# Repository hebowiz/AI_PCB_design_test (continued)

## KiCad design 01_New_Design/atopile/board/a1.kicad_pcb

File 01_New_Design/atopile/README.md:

# A-1 atopile設計

TXD/RXD/RTS/CTSのUSB-UART基板です。ユーザー指示により板厚を1.6 mmへ変更しました。22×50 mm、2層、全部品を表面に配置しています。

最終ERC/DRCは違反0件、未配線0件です。ただし、USB差動配線、水晶周辺、ビアとパッドの重なり、機械寸法・実装条件の確認が残っています。製造承認済みではありません。詳細は[設計結果](reports/design_review.md)を参照してください。

| 成果物 | パス |
| --- | --- |
| 最終PCB | `board/a1.kicad_pcb` |
| プロジェクト・回路図 | `board/a1.kicad_pro`、`board/a1.kicad_sch` |
| atopile回路 | `board/main.ato`、`board/parts/parts.ato` |
| 接続・配置の原記述 | `scripts/design.py`、`board/design.json` |
| 回路図PDF | `reports/schematic.pdf` |
| 裸基板の画像 | `reports/board-top.png` |
| 表裏の配線図 | `reports/board-front.svg`、`reports/board-back.svg` |
| 検査結果 | `reports/erc.json`、`reports/drc.json`、`reports/connectivity.json` |
| 部品表・ピン接続 | `reports/bom.csv`、`reports/pin_net.csv` |
| 製造レビュー用 | `manufacturing/review-only/`、`manufacturing/A1-REVIEW-ONLY.zip` |
| 経緯 | `reports/work_log.md`、`reports/decision_log.md`、`reports/discussion_log.md` |

## 実行環境と再検査

atopileは`docs/atopile_recovery.md`で修復された0.15.8を使います。`scripts/ato.ps1`は共有Git管理ディレクトリから元リポジトリの`.setup-local/atopile-rebuild`を見つけ、設定・ログをA-1の`.local/`へ分離します。別の配置では`A1_ATOPILE_REBUILD`で指定できます。通常のPATHにある`ato`は使用していません。

KiCadは10.0.8、同梱Pythonは3.11.5、Freeroutingは2.1.0、Javaは21.0.13.9です。次のコマンドはリポジトリのルートから実行します。

```powershell
$cli = "$env:LOCALAPPDATA/Programs/KiCad/10.0/bin/kicad-cli.exe"
$py = "$env:LOCALAPPDATA/Programs/KiCad/10.0/bin/python.exe"
$env:PYTHONUTF8 = '1'
& $cli sch erc --format json --exit-code-violations -o 01_New_Design/atopile/reports/erc.json 01_New_Design/atopile/board/a1.kicad_sch
& $cli sch export netlist --format kicadxml -o 01_New_Design/atopile/reports/schematic.net.xml 01_New_Design/atopile/board/a1.kicad_sch
& $py 01_New_Design/atopile/scripts/check_connectivity.py
& $cli pcb drc --severity-all --format json --exit-code-violations -o 01_New_Design/atopile/reports/drc.json 01_New_Design/atopile/board/a1.kicad_pcb
& $py 01_New_Design/atopile/scripts/layout.py verify
& ./01_New_Design/atopile/scripts/manufacturing.ps1
```

製造出力スクリプトはファイルをローカルで生成するだけで、発注やアップロードはしません。出力の内容と使用条件は`manufacturing/README.md`を参照してください。

## 回路生成と配置・配線の再現範囲

`scripts/design.py`は原記述からatomic部品、BOM、接続マニフェストを生成します。続く`./01_New_Design/atopile/scripts/ato.ps1 build --verbose`は`board/layouts/default/default.kicad_pcb`を生成します。最終PCBとは別ファイルです。

`scripts/layout.py prep`は配置とUSB固定配線を作り、`board/a1.kicad_pcb`を上書きします。完成済みPCBや人が変更したPCBにそのまま実行しないでください。今回の最終配線はFreeroutingのSESを取り込んだ後、未接続とGND、サーマル接続を補修した結果です。生成から最終状態までを一度に再現する単一コマンドは用意していません。

初回DSN/SESは`board/a1.dsn`と`board/a1.ses`です。Freerouting単独の未配線0は、KiCad取り込み後の未配線0を意味しません。最終成果物は補修後の`board/a1.kicad_pcb`です。`repair.dsn`と`repair2.dsn`は完走しなかった追加配線の入力証跡です。

FreeroutingはA-1内の一時ディレクトリを作業ディレクトリにし、次の条件で実行しました。

```text
java -Xmx6g -Djava.awt.headless=true -jar freerouting-2.1.0.jar -de input.dsn -do output.ses -mp 30 -mt 2 -da -l en --gui.enabled=false --user_data_path=<A-1内の作業ディレクトリ>
```

`freerouting.json`ではGUIとoptimizerを無効にし、profileのemail/idを空にしました。パス数の指定に反して継続する挙動があったため、停滞した試行は中断しています。ログは`reports/router-attempt*.log`に保存しました。

最終フットプリントは`board/A1.pretty`に保存しています。元のatomic部品のフットプリントに対して、シルクを整理し、5パッドのGNDゾーン接続を直接接続へ変更しました。銅箔パッドの位置・番号・寸法は変更していません。ローカルライブラリとの照合も含めてDRCを実行しています。

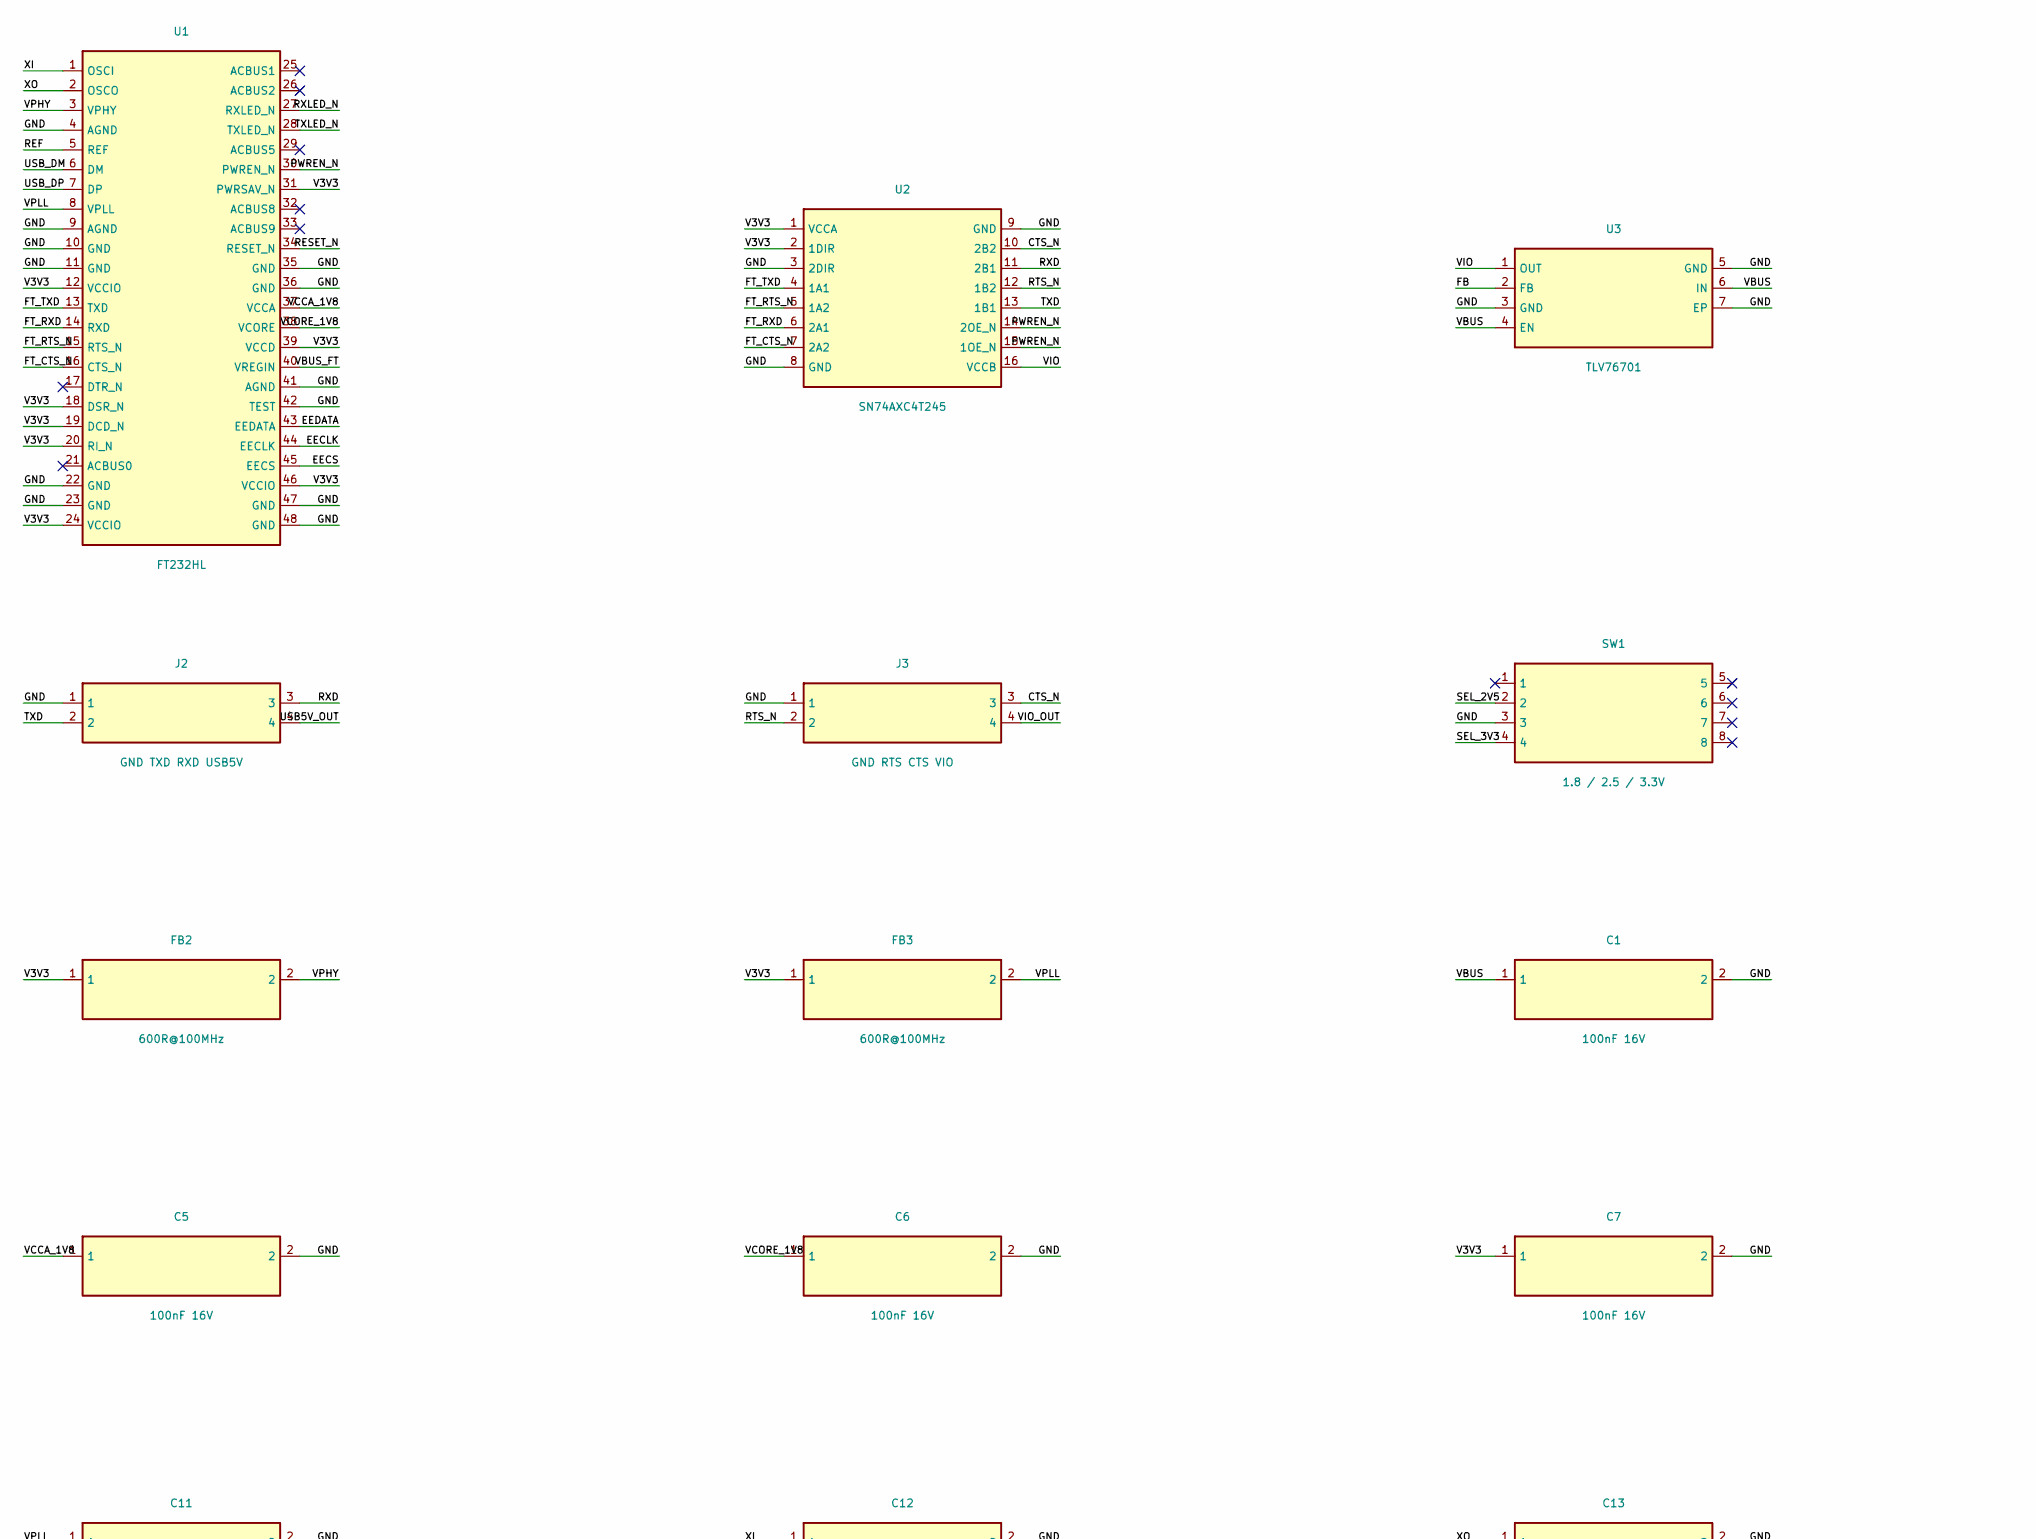
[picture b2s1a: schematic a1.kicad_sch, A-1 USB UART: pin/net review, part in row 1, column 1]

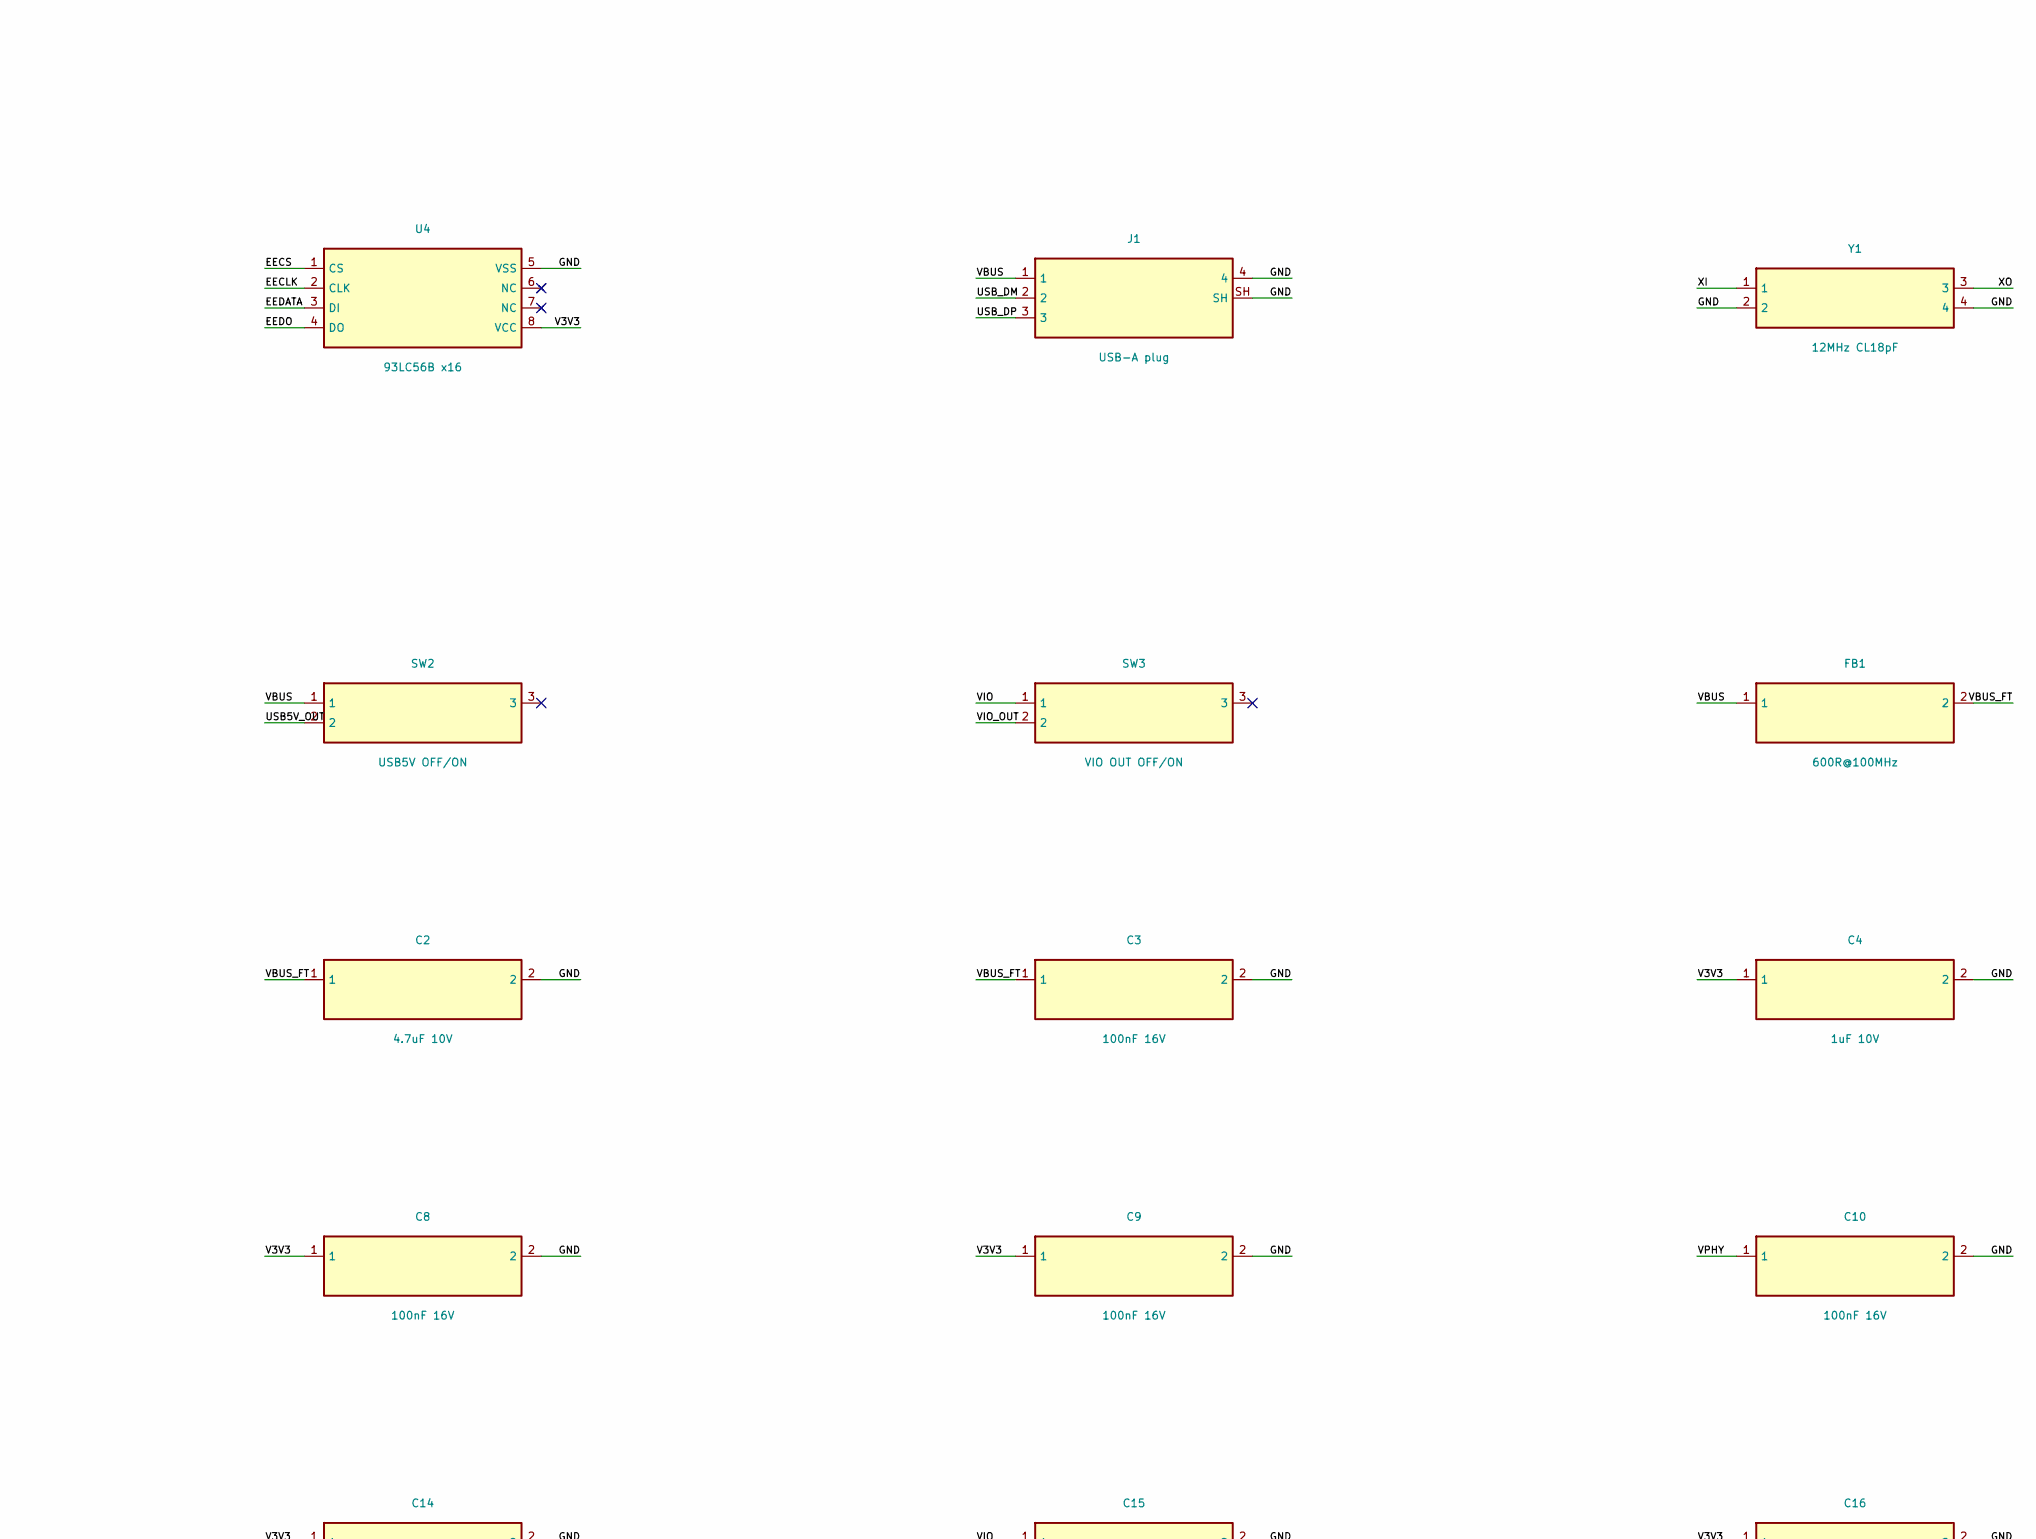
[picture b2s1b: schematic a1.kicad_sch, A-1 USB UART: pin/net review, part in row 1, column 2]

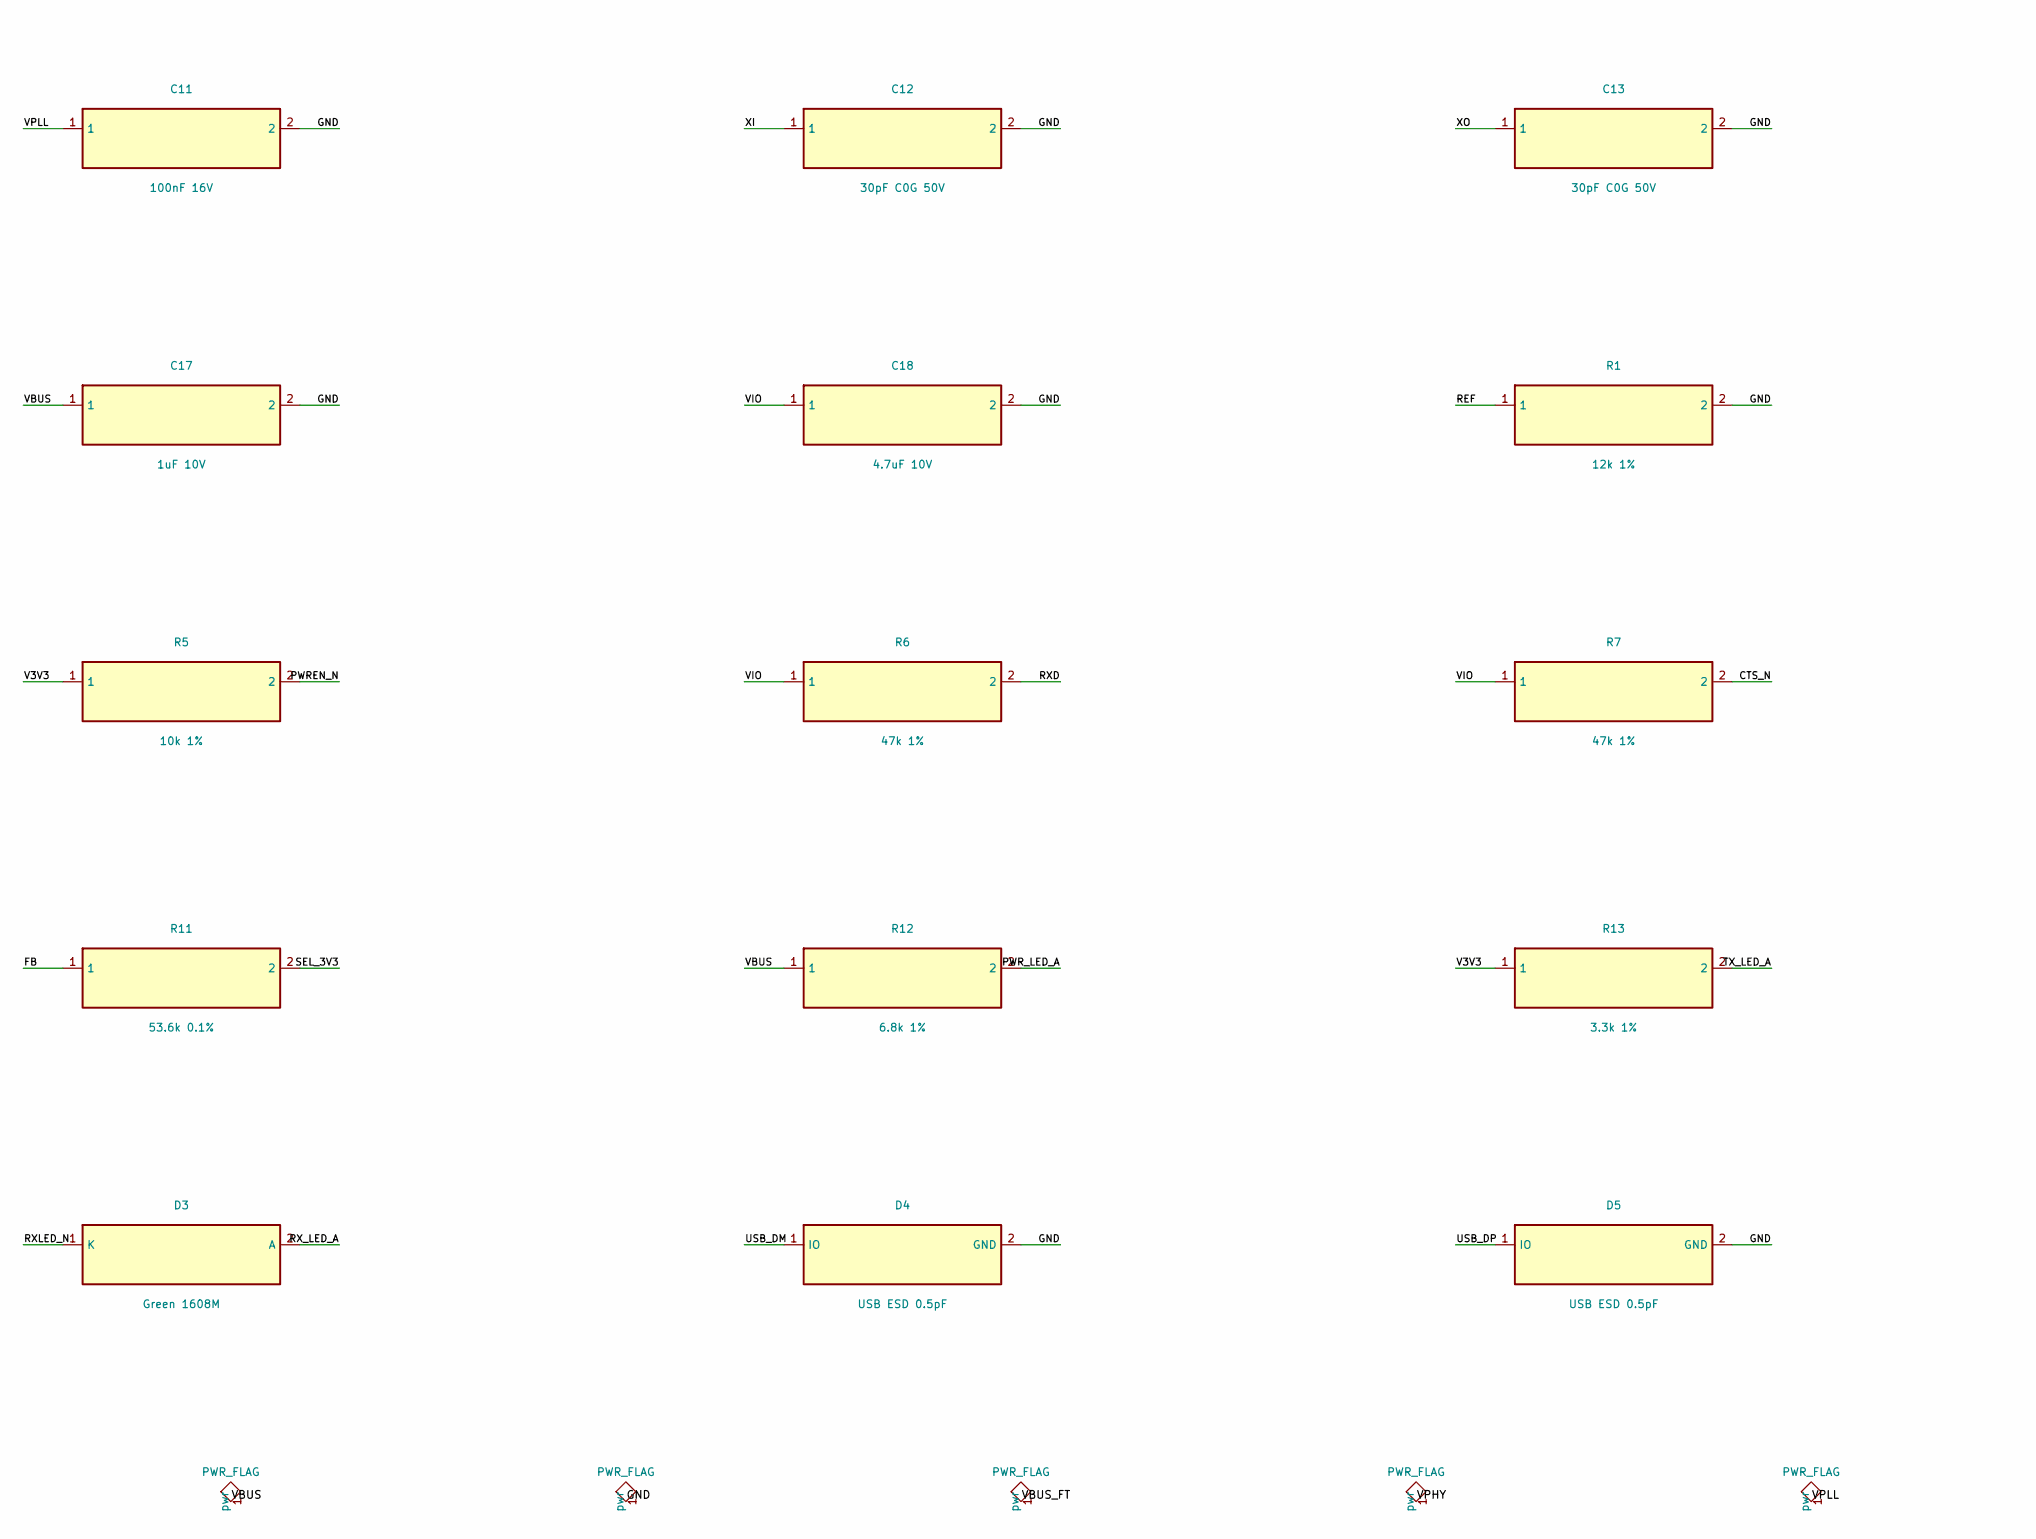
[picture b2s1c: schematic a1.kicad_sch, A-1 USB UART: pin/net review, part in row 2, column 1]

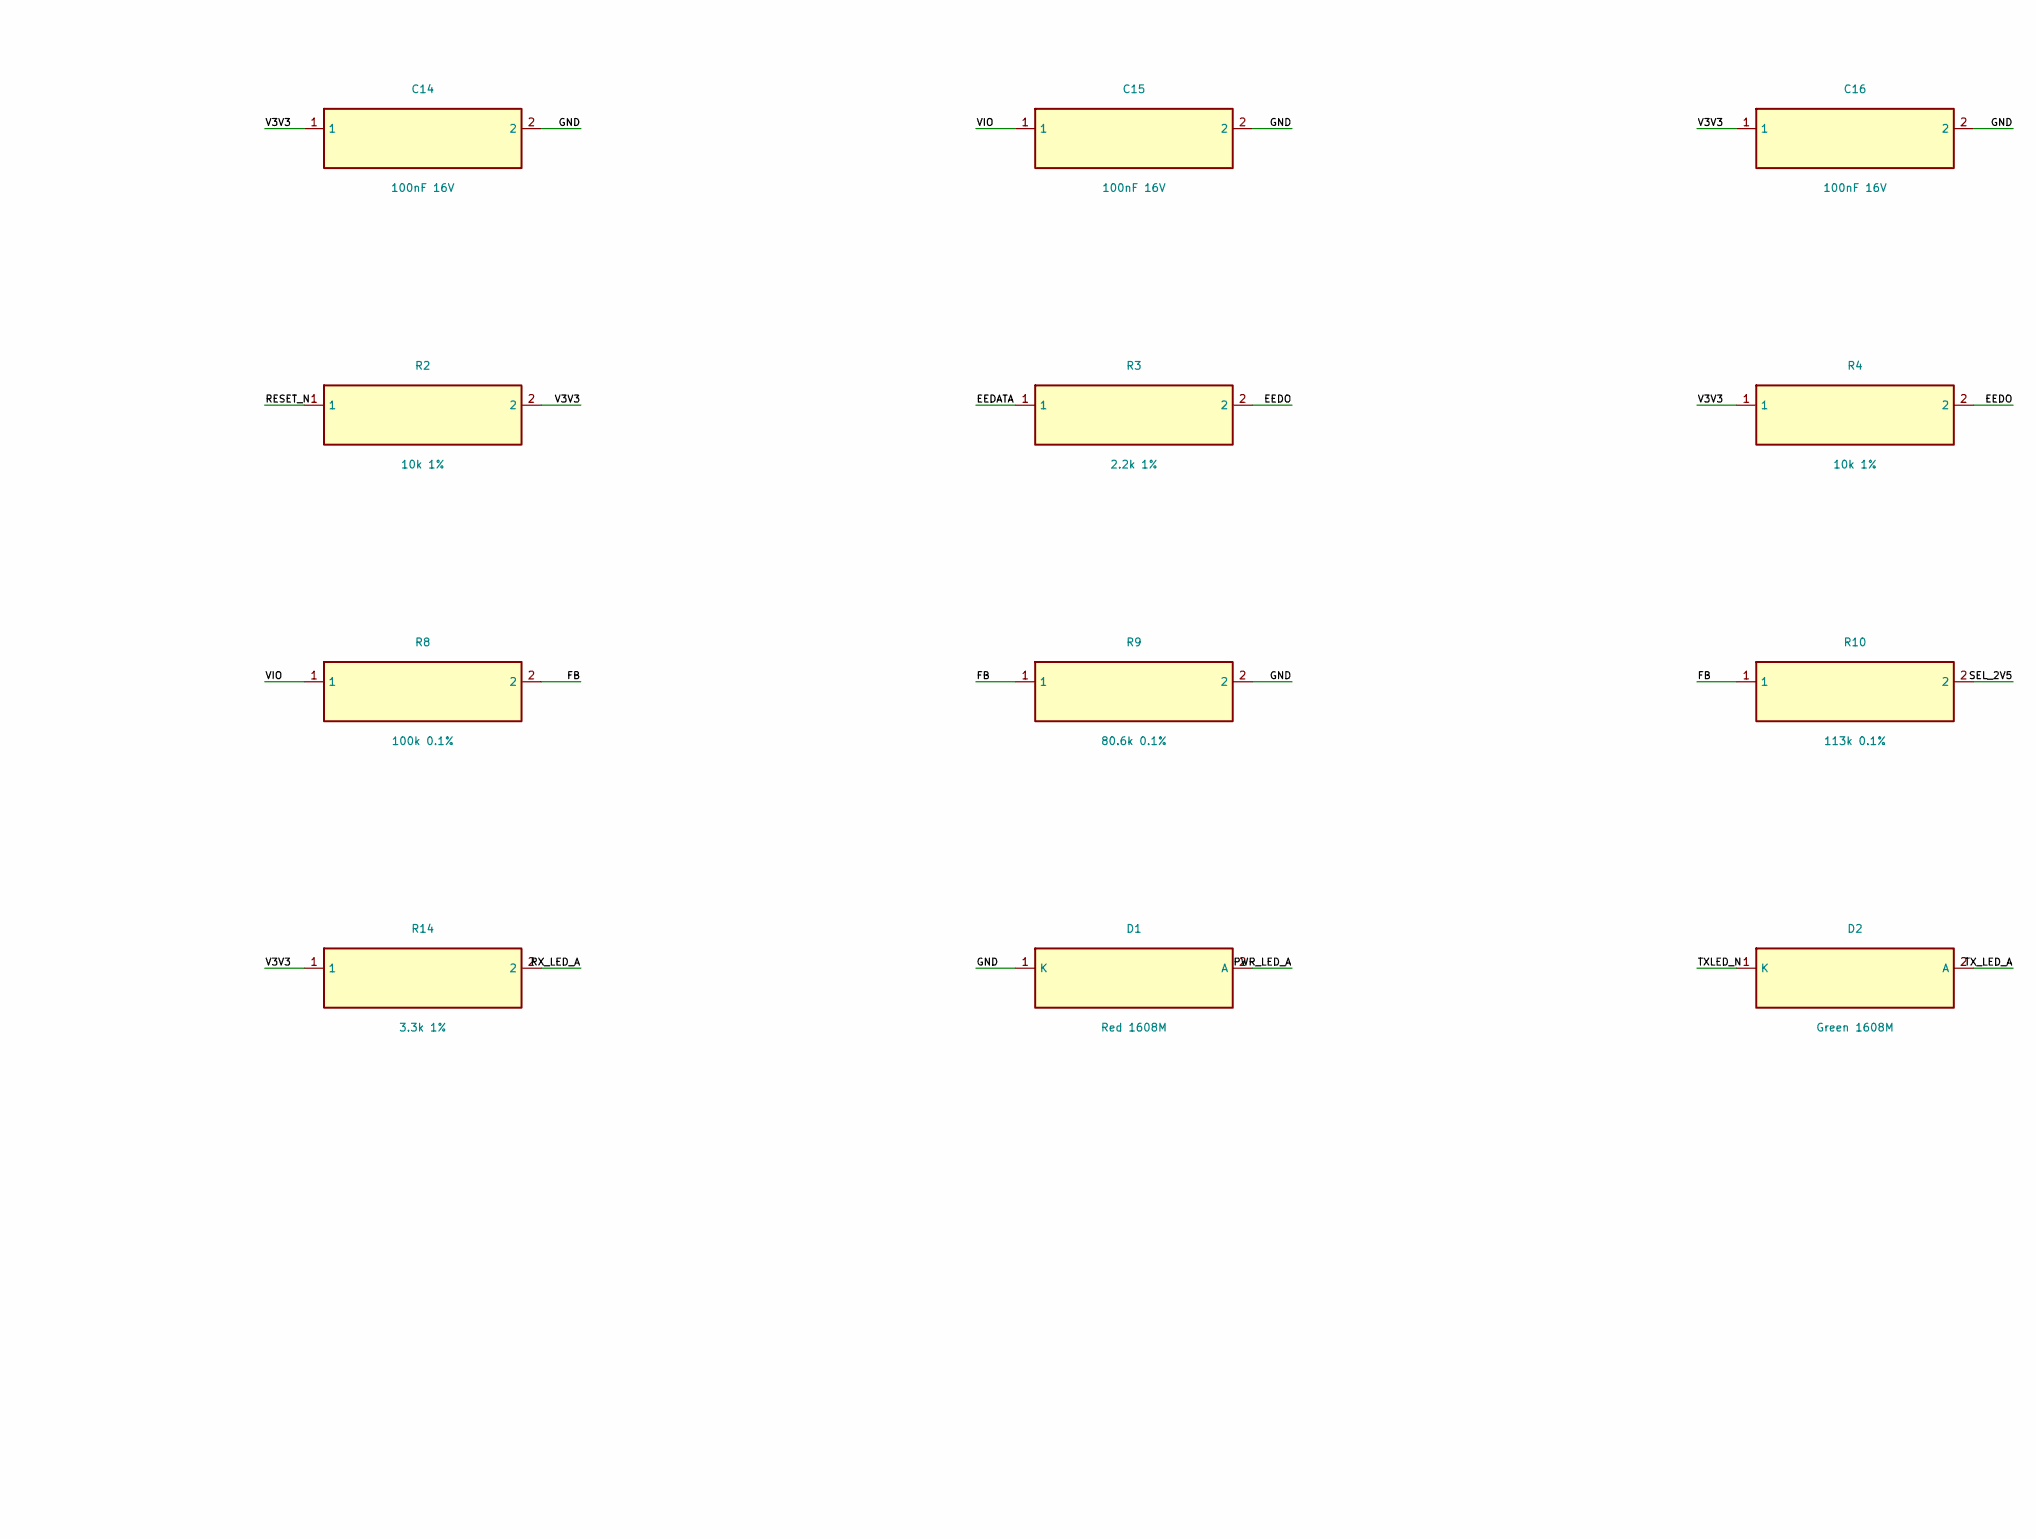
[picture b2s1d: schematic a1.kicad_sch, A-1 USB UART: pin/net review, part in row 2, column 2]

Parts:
C1: 100nF 16V; C1; MPN GRM155R71C104KA88D
C2: 4.7uF 10V; C2; MPN GRM188R61A475KE15D
C3: 100nF 16V; C3; MPN GRM155R71C104KA88D
C4: 1uF 10V; C4; MPN GRM188R61A105KA61D
C5: 100nF 16V; C5; MPN GRM155R71C104KA88D
C6: 100nF 16V; C6; MPN GRM155R71C104KA88D
C7: 100nF 16V; C7; MPN GRM155R71C104KA88D
C8: 100nF 16V; C8; MPN GRM155R71C104KA88D
C9: 100nF 16V; C9; MPN GRM155R71C104KA88D
C10: 100nF 16V; C10; MPN GRM155R71C104KA88D
C11: 100nF 16V; C11; MPN GRM155R71C104KA88D
C12: 30pF C0G 50V; C12; MPN GRM1555C1H300JA01D
C13: 30pF C0G 50V; C13; MPN GRM1555C1H300JA01D
C14: 100nF 16V; C14; MPN GRM155R71C104KA88D
C15: 100nF 16V; C15; MPN GRM155R71C104KA88D
C16: 100nF 16V; C16; MPN GRM155R71C104KA88D
C17: 1uF 10V; C17; MPN GRM188R61A105KA61D
C18: 4.7uF 10V; C18; MPN GRM188R61A475KE15D
D1: Red 1608M; D1; MPN LTST-C190KRKT
D2: Green 1608M; D2; MPN LTST-C190KGKT
D3: Green 1608M; D3; MPN LTST-C190KGKT
D4: USB ESD 0.5pF; D4; MPN TPD1E05U06DYAR
D5: USB ESD 0.5pF; D5; MPN TPD1E05U06DYAR
FB1: 600R@100MHz; FB1; MPN BLM15AG601SN1D
FB2: 600R@100MHz; FB2; MPN BLM15AG601SN1D
FB3: 600R@100MHz; FB3; MPN BLM15AG601SN1D
J1: USB-A plug; J1; MPN 0480372200
J2: GND TXD RXD USB5V; J2; MPN TSM-104-01-L-SH
J3: GND RTS CTS VIO; J3; MPN TSM-104-01-L-SV
R1: 12k 1%; R1; MPN RC0402FR-0712KL
R2: 10k 1%; R2; MPN RC0402FR-0710KL
R3: 2.2k 1%; R3; MPN RC0402FR-072K2L
R4: 10k 1%; R4; MPN RC0402FR-0710KL
R5: 10k 1%; R5; MPN RC0402FR-0710KL
R6: 47k 1%; R6; MPN RC0402FR-0747KL
R7: 47k 1%; R7; MPN RC0402FR-0747KL
R8: 100k 0.1%; R8; MPN RT0402BRD07100KL
R9: 80.6k 0.1%; R9; MPN RT0402BRD0780K6L
R10: 113k 0.1%; R10; MPN RT0402BRD07113KL
R11: 53.6k 0.1%; R11; MPN RT0402BRD0753K6L
R12: 6.8k 1%; R12; MPN RC0402FR-076K8L
R13: 3.3k 1%; R13; MPN RC0402FR-073K3L
R14: 3.3k 1%; R14; MPN RC0402FR-073K3L
SW1: 1.8 / 2.5 / 3.3V; SW1; MPN JS203011SCQN
SW2: USB5V OFF/ON; SW2; MPN PCM12SMTR
SW3: VIO OUT OFF/ON; SW3; MPN PCM12SMTR
U1: FT232HL; U1; MPN FT232HL-REEL
U2: SN74AXC4T245; U2; MPN SN74AXC4T245PWR
U3: TLV76701; U3; MPN TLV76701DRVR
U4: 93LC56B x16; U4; MPN 93LC56BT-I/SN
Y1: 12MHz CL18pF; Y1; MPN ABM8-12.000MHZ-B1U-T

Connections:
1: SW1.1
3: SW2.3
5: SW1.5
6: U4.6 (NC)
7: U4.7 (NC)
8: SW1.8
17: U1.17 (DTR_N)
21: U1.21 (ACBUS0)
25: U1.25 (ACBUS1)
26: U1.26 (ACBUS2)
29: U1.29 (ACBUS5)
32: U1.32 (ACBUS8)
33: U1.33 (ACBUS9)
CTS_N: J3.3, R7.2, U2.10 (2B2)
EECLK: U1.44 (EECLK), U4.2 (CLK)
EECS: U1.45 (EECS), U4.1 (CS)
EEDATA: R3.1, U1.43 (EEDATA), U4.3 (DI)
EEDO: R3.2, R4.2, U4.4 (DO)
FB: R8.2, R9.1, R10.1, R11.1, U3.2 (FB)
FT_CTS_N: U1.16 (CTS_N), U2.7 (2A2)
FT_RTS_N: U1.15 (RTS_N), U2.5 (1A2)
FT_RXD: U1.14 (RXD), U2.6 (2A1)
FT_TXD: U1.13 (TXD), U2.4 (1A1)
GND: C1.2, C2.2, C3.2, C4.2, C5.2, C6.2, C7.2, C8.2, C9.2, C10.2, C11.2, C12.2, C13.2, C14.2, C15.2, C16.2, C17.2, C18.2, D1.1 (K), D4.2 (GND), D5.2 (GND), J1.4, J1.SH, J2.1, J3.1, R1.2, R9.2, SW1.3, U1.4 (AGND), U1.9 (AGND), U1.10 (GND), U1.11 (GND), U1.22 (GND), U1.23 (GND), U1.35 (GND), U1.36 (GND), U1.41 (AGND), U1.42 (TEST), U1.47 (GND), U1.48 (GND), U2.3 (2DIR), U2.8 (GND), U2.9 (GND), U3.3 (GND), U3.5 (GND), U3.7 (EP), U4.5 (VSS), Y1.2, Y1.4
PWREN_N: R5.2, U1.30 (PWREN_N), U2.14 (2OE_N), U2.15 (1OE_N)
PWR_LED_A: D1.2 (A), R12.2
REF: R1.1, U1.5 (REF)
RESET_N: R2.1, U1.34 (RESET_N)
RTS_N: J3.2, U2.12 (1B2)
RXD: J2.3, R6.2, U2.11 (2B1)
RXLED_N: D3.1 (K), U1.27 (RXLED_N)
RX_LED_A: D3.2 (A), R14.2
SEL_2V5: R10.2, SW1.2
SEL_3V3: R11.2, SW1.4
TXD: J2.2, U2.13 (1B1)
TXLED_N: D2.1 (K), U1.28 (TXLED_N)
TX_LED_A: D2.2 (A), R13.2
USB5V_OUT: J2.4, SW2.2
USB_DM: D4.1 (IO), J1.2, U1.6 (DM)
USB_DP: D5.1 (IO), J1.3, U1.7 (DP)
V3V3: C4.1, C7.1, C8.1, C9.1, C14.1, C16.1, FB2.1, FB3.1, R2.2, R4.1, R5.1, R13.1, R14.1, U1.12 (VCCIO), U1.18 (DSR_N), U1.19 (DCD_N), U1.20 (RI_N), U1.24 (VCCIO), U1.31 (PWRSAV_N), U1.39 (VCCD), U1.46 (VCCIO), U2.1 (VCCA), U2.2 (1DIR), U4.8 (VCC)
VBUS: C1.1, C17.1, FB1.1, J1.1, R12.1, SW2.1, U3.4 (EN), U3.6 (IN)
VBUS_FT: C2.1, C3.1, FB1.2, U1.40 (VREGIN)
VCCA_1V8: C5.1, U1.37 (VCCA)
VCORE_1V8: C6.1, U1.38 (VCORE)
VIO: C15.1, C18.1, R6.1, R7.1, R8.1, SW3.1, U2.16 (VCCB), U3.1 (OUT)
VIO_OUT: J3.4, SW3.2
VPHY: C10.1, FB2.2, U1.3 (VPHY)
VPLL: C11.1, FB3.2, U1.8 (VPLL)
XI: C12.1, U1.1 (OSCI), Y1.1
XO: C13.1, U1.2 (OSCO), Y1.3
vio_switch-3: SW3.3
voltage_select-6: SW1.6
voltage_select-7: SW1.7

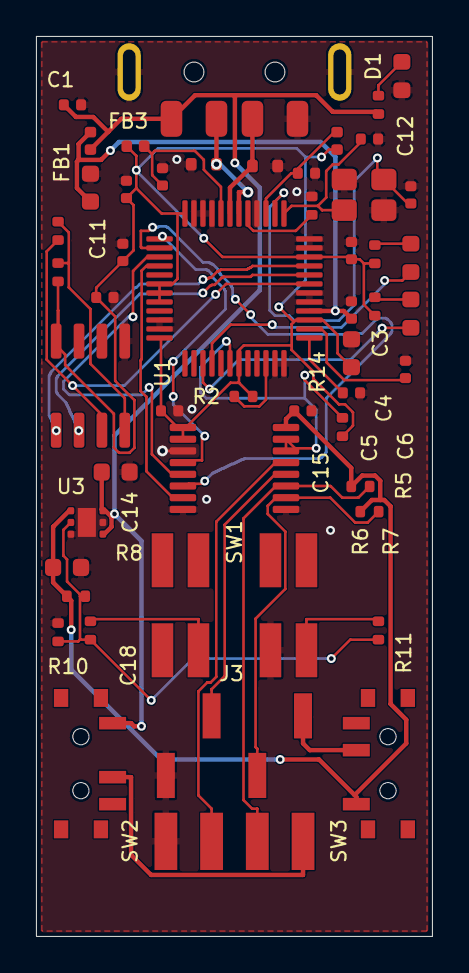
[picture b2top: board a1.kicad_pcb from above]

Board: 2 copper layers, 22.0 x 50.0 mm, 51 parts (0 on the bottom side), 38 nets.

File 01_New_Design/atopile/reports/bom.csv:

Reference,Instance,Value,Manufacturer,MPN,Footprint,Quantity,Notes
J1,usb,USB-A plug,Molex,0480372200,Connector_USB:USB_A_Molex_48037-2200_Horizontal,1,"User changed A-1 thickness to 1.6 mm, matching the manufacturer recommendation."
U1,ft232h,FT232HL,FTDI,FT232HL-REEL,Package_QFP:LQFP-48_7x7mm_P0.5mm,1,
U2,translator,SN74AXC4T245,Texas Instruments,SN74AXC4T245PWR,Package_SO:TSSOP-16_4.4x5mm_P0.65mm,1,
U3,vio_ldo,TLV76701,Texas Instruments,TLV76701DRVR,Package_SON:WSON-6-1EP_2x2mm_P0.65mm_EP1x1.6mm,1,
U4,eeprom,93LC56B x16,Microchip,93LC56BT-I/SN,Package_SO:SOIC-8_3.9x4.9mm_P1.27mm,1,
Y1,crystal,12MHz CL18pF,Abracon,ABM8-12.000MHZ-B1U-T,Crystal:Crystal_SMD_3225-4Pin_3.2x2.5mm,1,
J2,uart_header,GND TXD RXD USB5V,Samtec,TSM-104-01-L-SH,A1:TSM_104_SH,1,Locally drawn SMT right-angle footprint; manufacturer drawing review recorded separately.
J3,aux_header,GND RTS CTS VIO,Samtec,TSM-104-01-L-SV,Connector_PinHeader_2.54mm:PinHeader_1x04_P2.54mm_Vertical_SMD_Pin1Left,1,
SW1,voltage_select,1.8 / 2.5 / 3.3V,C&K,JS203011SCQN,A1:JS203011SCQN,1,Only switch with USB disconnected. Contact-break default is 1.8V.
SW2,usb5v_switch,USB5V OFF/ON,C&K,PCM12SMTR,Button_Switch_SMD:SW_SPDT_PCM12,1,
SW3,vio_switch,VIO OUT OFF/ON,C&K,PCM12SMTR,Button_Switch_SMD:SW_SPDT_PCM12,1,
FB1,vbus_bead,600R@100MHz,Murata,BLM15AG601SN1D,Inductor_SMD:L_0402_1005Metric,1,
FB2,phy_bead,600R@100MHz,Murata,BLM15AG601SN1D,Inductor_SMD:L_0402_1005Metric,1,
FB3,pll_bead,600R@100MHz,Murata,BLM15AG601SN1D,Inductor_SMD:L_0402_1005Metric,1,
C1,vbus_in,100nF 16V,Murata,GRM155R71C104KA88D,Capacitor_SMD:C_0402_1005Metric,1,
C2,ft_bulk,4.7uF 10V,Murata,GRM188R61A475KE15D,Capacitor_SMD:C_0603_1608Metric,1,
C3,ft_vreg,100nF 16V,Murata,GRM155R71C104KA88D,Capacitor_SMD:C_0402_1005Metric,1,
C4,ft_3v3,1uF 10V,Murata,GRM188R61A105KA61D,Capacitor_SMD:C_0603_1608Metric,1,
C5,ft_vcca,100nF 16V,Murata,GRM155R71C104KA88D,Capacitor_SMD:C_0402_1005Metric,1,
C6,ft_vcore,100nF 16V,Murata,GRM155R71C104KA88D,Capacitor_SMD:C_0402_1005Metric,1,
C7,ft_io12,100nF 16V,Murata,GRM155R71C104KA88D,Capacitor_SMD:C_0402_1005Metric,1,
C8,ft_io24,100nF 16V,Murata,GRM155R71C104KA88D,Capacitor_SMD:C_0402_1005Metric,1,
C9,ft_io46,100nF 16V,Murata,GRM155R71C104KA88D,Capacitor_SMD:C_0402_1005Metric,1,
C10,phy_dec,100nF 16V,Murata,GRM155R71C104KA88D,Capacitor_SMD:C_0402_1005Metric,1,
C11,pll_dec,100nF 16V,Murata,GRM155R71C104KA88D,Capacitor_SMD:C_0402_1005Metric,1,
C12,x1_load,30pF C0G 50V,Murata,GRM1555C1H300JA01D,Capacitor_SMD:C_0402_1005Metric,1,
C13,x2_load,30pF C0G 50V,Murata,GRM1555C1H300JA01D,Capacitor_SMD:C_0402_1005Metric,1,
C14,level_a,100nF 16V,Murata,GRM155R71C104KA88D,Capacitor_SMD:C_0402_1005Metric,1,
C15,level_b,100nF 16V,Murata,GRM155R71C104KA88D,Capacitor_SMD:C_0402_1005Metric,1,
C16,eeprom_dec,100nF 16V,Murata,GRM155R71C104KA88D,Capacitor_SMD:C_0402_1005Metric,1,
C17,ldo_in,1uF 10V,Murata,GRM188R61A105KA61D,Capacitor_SMD:C_0603_1608Metric,1,
C18,ldo_out,4.7uF 10V,Murata,GRM188R61A475KE15D,Capacitor_SMD:C_0603_1608Metric,1,
R1,ref_res,12k 1%,Yageo,RC0402FR-0712KL,Resistor_SMD:R_0402_1005Metric,1,
R2,reset_pullup,10k 1%,Yageo,RC0402FR-0710KL,Resistor_SMD:R_0402_1005Metric,1,
R3,eeprom_do_series,2.2k 1%,Yageo,RC0402FR-072K2L,Resistor_SMD:R_0402_1005Metric,1,
R4,eeprom_do_pullup,10k 1%,Yageo,RC0402FR-0710KL,Resistor_SMD:R_0402_1005Metric,1,
R5,oe_pullup,10k 1%,Yageo,RC0402FR-0710KL,Resistor_SMD:R_0402_1005Metric,1,
R6,rx_pullup,47k 1%,Yageo,RC0402FR-0747KL,Resistor_SMD:R_0402_1005Metric,1,
R7,cts_pullup,47k 1%,Yageo,RC0402FR-0747KL,Resistor_SMD:R_0402_1005Metric,1,
R8,fb_top,100k 0.1%,Yageo,RT0402BRD07100KL,Resistor_SMD:R_0402_1005Metric,1,
R9,fb_bottom,80.6k 0.1%,Yageo,RT0402BRD0780K6L,Resistor_SMD:R_0402_1005Metric,1,
R10,fb_2v5,113k 0.1%,Yageo,RT0402BRD07113KL,Resistor_SMD:R_0402_1005Metric,1,
R11,fb_3v3,53.6k 0.1%,Yageo,RT0402BRD0753K6L,Resistor_SMD:R_0402_1005Metric,1,
R12,power_led_res,6.8k 1%,Yageo,RC0402FR-076K8L,Resistor_SMD:R_0402_1005Metric,1,
R13,tx_led_res,3.3k 1%,Yageo,RC0402FR-073K3L,Resistor_SMD:R_0402_1005Metric,1,
R14,rx_led_res,3.3k 1%,Yageo,RC0402FR-073K3L,Resistor_SMD:R_0402_1005Metric,1,
D1,power_led,Red 1608M,Lite-On,LTST-C190KRKT,LED_SMD:LED_0603_1608Metric,1,
D2,tx_led,Green 1608M,Lite-On,LTST-C190KGKT,LED_SMD:LED_0603_1608Metric,1,
D3,rx_led,Green 1608M,Lite-On,LTST-C190KGKT,LED_SMD:LED_0603_1608Metric,1,
D4,usb_dm_esd,USB ESD 0.5pF,Texas Instruments,TPD1E05U06DYAR,Diode_SMD:D_SOD-523,1,
D5,usb_dp_esd,USB ESD 0.5pF,Texas Instruments,TPD1E05U06DYAR,Diode_SMD:D_SOD-523,1,

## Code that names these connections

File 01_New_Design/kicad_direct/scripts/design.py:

"""A-2 circuit data. Units: mm; PCB origin is (100, 100), top view.

User amendment: only TXD/RXD/RTS/CTS are exposed. No atopile dependency.
"""
from pathlib import Path
import os

ROOT = Path(__file__).resolve().parents[1]
KICAD = Path(os.environ.get('KICAD_ROOT', str(Path(os.environ['LOCALAPPDATA'])/'Programs/KiCad/10.0')))
PARTS = []

def part(ref, value, lib, footprint, nets, xy, angle=0, mpn='', note='', group='support'):
    PARTS.append(dict(ref=ref,value=value,lib=lib,footprint=footprint,
                      nets={str(k):v for k,v in nets.items()},xy=xy,angle=angle,
                      mpn=mpn,note=note,group=group))

part('U1','FT232HL','A2:FT232HL_UART','Package_QFP:LQFP-48_7x7mm_P0.5mm',{
  1:'XTAL_IN',2:'XTAL_OUT',3:'VPHY',4:'GND',5:'REF12K',6:'USB_D-',7:'USB_D+',8:'VPLL',9:'GND',10:'GND',11:'GND',12:'+3V3',
  13:'FT_TXD',14:'FT_RXD',15:'FT_RTS_N',16:'FT_CTS_N',17:None,18:None,19:None,20:None,21:None,22:'GND',23:'GND',24:'+3V3',
  25:None,26:None,27:'RXLED_N',28:'TXLED_N',29:None,30:None,31:None,32:'PWREN_N',33:None,34:'RESET_N',35:'GND',36:'GND',
  37:'VCCA_1V8',38:'VCORE_1V8',39:'+3V3',40:'+3V3',41:'GND',42:'GND',43:'EE_DATA',44:'EE_CLK',45:'EE_CS',46:'+3V3',47:'GND',48:'GND'},(11,16),270,'FT232HL-REEL','UART mode; EEPROM programming required','bridge')
part('U2','SN74AXC4T245PWR','A2:SN74AXC4T245','Package_SO:TSSOP-16_4.4x5mm_P0.65mm',{
 1:'+3V3',2:'+3V3',3:'GND',4:'FT_TXD',5:'FT_RTS_N',6:'FT_RXD',7:'FT_CTS_N',8:'GND',9:'GND',10:'CTS_N',11:'RXD',12:'RTS_N',13:'TXD',14:'PWREN_N',15:'PWREN_N',16:'VIO'},(11,29),0,'SN74AXC4T245PWR','1DIR=1 (TX/RTS); 2DIR=0 (RX/CTS)','uart')
part('U3','AP2112K-3.3','Regulator_Linear:AP2112K-3.3','Package_TO_SOT_SMD:SOT-23-5',{1:'USB5V',2:'GND',3:'USB5V',4:None,5:'+3V3'},(18.5,8.5),0,'AP2112K-3.3TRG1','Fixed bridge supply','power')
part('U4','TLV75801PDBV','Regulator_Linear:TLV75801PDBV','Package_TO_SOT_SMD:SOT-23-5',{1:'USB5V',2:'GND',3:'PWR_EN',4:'FB',5:'VIO'},(11,37),0,'TLV75801PDBVR','1.8/2.5/3.3 V; change SW1 only while unpowered','power')
part('U5','93LC56B','Memory_EEPROM:93LCxxB','Package_SO:MSOP-8_3x3mm_P0.65mm',{1:'EE_CS',2:'EE_CLK',3:'EE_DATA',4:'EE_DO',5:'GND',6:None,7:None,8:'+3V3'},(4.5,23),0,'93LC56B-I/MS','16-bit organization','bridge')
part('U6','TPS22919DCK','Power_Management:TPS22919DCK','Package_TO_SOT_SMD:SOT-363_SC-70-6',{1:'USB5V',2:'GND',3:'PWR_EN',4:None,5:'QOD',6:'USB5V_ENABLED'},(3.5,34),0,'TPS22919DCKR','USB external power disabled before enumeration / in suspend','power')
part('Q1','2N7002','Transistor_FET:2N7002','Package_TO_SOT_SMD:SOT-23',{1:'PWREN_N',2:'GND',3:'PWR_EN'},(17,23),0,'2N7002P,215','Invert PWREN# for load switch and adjustable LDO','power')
part('D1','TPD2EUSB30','Power_Protection:TPD2EUSB30','Package_TO_SOT_SMD:Texas_DRT-3',{1:'USB_D+',2:'USB_D-',3:'GND'},(11,7.5),0,'TPD2EUSB30DRTR','USB ESD','bridge')
part('J1','USB-A PLUG','A2:USB_A_PLUG','Connector_USB:USB_A_Molex_48037-2200_Horizontal',{1:'USB5V',2:'USB_D-',3:'USB_D+',4:'GND','SH':'GND'},(11,-7.225),90,'0480372200','Vendor recommended 1.6 mm PCB adopted; mechanical fit requires prototype check','bridge')
part('J2','GND TXD RXD 5V','Connector_Generic:Conn_01x04','A2:TSM_104_SH_PROVISIONAL',{1:'GND',2:'TXD',3:'RXD',4:'USB5V_OUT'},(11,47),0,'TSM-104-01-T-SH','PROVISIONAL footprint; manufacturer land-pattern confirmation required','uart')
part('J3','RTS CTS GND VIO','Connector_Generic:Conn_01x04','Connector_PinHeader_2.54mm:PinHeader_1x04_P2.54mm_Vertical_SMD_Pin1Left',{1:'RTS_N',2:'CTS_N',3:'GND',4:'VIO_OUT'},(11,42),90,'TSM-104-01-T-SV','Generic KiCad land pattern; confirm exact part before fab','uart')
part('SW1','1V8 / 2V5 / 3V3','A2:PCM13','Button_Switch_SMD:SW_SP3T_PCM13',{1:None,2:'FB_2V5',3:'GND',4:'FB_3V3'},(19.7,34),90,'PCM13SMTR','Common pin 3; pos1=1-3, pos2=2-3, pos3=3-4','power')
part('SW2','USB5V OUT','A2:PCM12','Button_Switch_SMD:SW_SPDT_PCM12',{1:None,2:'USB5V_OUT',3:'USB5V_ENABLED'},(2.3,42),270,'PCM12SMTR','Off/open or on; no external back-feed permitted','power')
part('SW3','VIO OUT','A2:PCM12','Button_Switch_SMD:SW_SPDT_PCM12',{1:None,2:'VIO_OUT',3:'VIO'},(19.7,44.5),90,'PCM12SMTR','Switches header supply only; UART remains enabled','power')
part('Y1','12MHz 18pF','Device:Crystal_GND24','Crystal:Crystal_SMD_3225-4Pin_3.2x2.5mm',{1:'XTAL_IN',2:'GND',3:'XTAL_OUT',4:'GND'},(4.3,10),0,'ABM8-12.000MHZ-B2-T','27 pF loads assume 4.5 pF stray; frequency/start-up requires measurement','bridge')

def r(ref,val,a,b,xy,angle=0,mpn='',note=''):
    part(ref,val,'Device:R','Resistor_SMD:R_0402_1005Metric',{1:a,2:b},xy,angle,mpn or f'Yageo RC0402FR-07 ({val}, 1%)',note)
def c(ref,val,a,xy,angle=0,large=False,mpn=''):
    part(ref,val,'Device:C',f'Capacitor_SMD:C_{"0603_1608" if large else "0402_1005"}Metric',{1:a,2:'GND'},xy,angle,mpn or ('GRM188R61A225KE34D' if val=='2.2u' else 'CL05B104KO5NNNC' if val=='100n' else 'C1005C0G1H270J050BA' if val=='27p' else 'CL05A105KA5NQNC'),'Capacitance at DC bias must meet regulator minimum')
r('R1','12k','REF12K','GND',(7,10.8),90,'RC0402FR-0712KL')
r('R2','10k','+3V3','RESET_N',(18,15),90,'RC0402FR-0710KL')
r('R3','10k','+3V3','EE_DO',(2,27),90,'RC0402FR-0710KL')
r('R4','2.2k','EE_DO','EE_DATA',(5,27),0,'RC0402FR-072K2L')
r('R5','10k','+3V3','PWREN_N',(17,26),0,'RC0402FR-0710KL')
r('R6','10k','+3V3','PWR_EN',(19.5,23),90,'RC0402FR-0710KL')
r('R7','22.6k','VIO','FB',(14.2,36),90,'RC0402FR-0722K6L')
r('R8','10k','FB','GND',(14.2,38.5),90,'RC0402FR-0710KL')
r('R9','17.8k','FB','FB_2V5',(16.3,33.5),90,'RC0402FR-0717K8L')
r('R10','8.25k','FB','FB_3V3',(16.3,37),90,'RC0402FR-078K25L')
r('R11','100k','VIO','RXD',(15.5,29),90,'RC0402FR-07100KL')
r('R12','100k','VIO','CTS_N',(15.5,31.5),90,'RC0402FR-07100KL')
r('R13','10k','USB5V','LED_PWR_A',(19,3),0,'RC0402FR-0710KL','About 0.3 mA red indicator')
r('R14','4.7k','+3V3','LED_TX_A',(18.5,18),90,'RC0402FR-074K7L','About 0.28 mA green indicator')
r('R15','4.7k','+3V3','LED_RX_A',(20.2,18),90,'RC0402FR-074K7L','About 0.28 mA green indicator')
r('R16','100','QOD','USB5V_ENABLED',(6,34),90,'RC0402FR-07100RL','Discharge resistor')
for ref,color,an,ka,xy,mpn in [('D2','RED','LED_PWR_A','GND',(19,5),'LTST-C190KRKT'),('D3','GREEN TX','LED_TX_A','TXLED_N',(18.5,20.5),'LTST-C190KGKT'),('D4','GREEN RX','LED_RX_A','RXLED_N',(20.2,20.5),'LTST-C190KGKT')]:
    part(ref,color,'Device:LED','LED_SMD:LED_0603_1608Metric',{1:ka,2:an},xy,90,mpn,'1608M; visual brightness unverified')

c('C1','1u','USB5V',(16,7),90)
c('C2','2.2u','+3V3',(18.5,11.5),0,True)
c('C3','100n','+3V3',(15,9.6),0)
c('C4','100n','+3V3',(4.5,15),90)
c('C5','100n','+3V3',(17.7,13),0)
c('C6','100n','+3V3',(11,22.5),0)
c('C7','100n','VCCA_1V8',(15,21.5),90)
c('C8','100n','VCORE_1V8',(13.3,21.5),90)
c('C9','100n','VPHY',(6,7),0)
c('C10','100n','VPLL',(13.5,9),90)
c('C11','1u','VPHY',(7.7,7),0)
c('C12','1u','VPLL',(15,7),90)
c('C13','27p','XTAL_IN',(2,7.8),90)
c('C14','27p','XTAL_OUT',(2,12.4),90)
c('C15','100n','+3V3',(4,19.3),0)
c('C16','100n','+3V3',(6.7,25.3),90)
c('C17','100n','VIO',(15.5,26.7),90)
c('C18','1u','USB5V',(8,34.5),0)
c('C19','2.2u','VIO',(10.7,33.8),0,True)
c('C20','1u','USB5V',(2.8,31.2),0)
c('C21','1u','USB5V_ENABLED',(5.5,36.5),90)
c('C22','100n','RESET_N',(20,15),90)
for ref,net,xy in [('FB1','VPHY',(9,8.8)),('FB2','VPLL',(13.5,6))]:
    part(ref,'600R@100MHz','Device:FerriteBead','Inductor_SMD:L_0402_1005Metric',{1:'+3V3',2:net},xy,0,'BLM15AG601SN1D','Local PHY / PLL filtering')

# Explicit ERC power sources after passive beads and the USB connector.
FLAGS = ['USB5V','GND','VPHY','VPLL']

# Placement refinement after initial KiCad DRC (no manual CAD edits occurred).
REVISED = {'J1':(11,-6.225),'C13':(1.6,7.2),'C14':(1.6,13),
           'C1':(16.3,5.8),'C11':(8,6.8),'C8':(13,23.8),'C7':(15.2,23.8),
           'Q1':(18.5,24),'R6':(20.5,26.4),'R5':(18.2,26.8),
           'C16':(7.2,24),'J3':(11,42.6),'R8':(14.2,38),
           'U4':(10.5,36.2),'C19':(10.7,33.8),'J3':(11,42.1),
           'FB2':(13,7.5),'C12':(20.5,12.3),'C16':(8.5,24),
           'C19':(10.7,33.5),'C18':(7,34.3),'R8':(14.7,37.4),
           'J2':(11,47.3),'J3':(11,42),'R7':(14.2,35.2),'C18':(8,32.6)}
for p in PARTS:
    if p['ref'] in REVISED:p['xy']=REVISED[p['ref']]
